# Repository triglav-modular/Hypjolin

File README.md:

# Hypjolin

The Hypjolin is a cross-modulating ultra-chaos generator device which combines Rob Hordijk’s Benjolin and Ian Fritz’s Hypster circuits. 
By merging the Benjolin’s stepped chaos with the Hypster’s smooth, fluctuating chaos, the Hypjolin produces remarkably unpredictable, yet controllable sonic outcomes.  
The integration of these two systems is facilitated through a banana jack patchbay, with blue banana jacks representing Benjolin outputs and purple ones denoting Hypster outputs. The black jacks serve as inputs. The patch bay is spaced for use with shorting bars.

Mouser Cart: https://www.mouser.com/ProjectManager/ProjectDetail.aspx?AccessID=39b2feea56

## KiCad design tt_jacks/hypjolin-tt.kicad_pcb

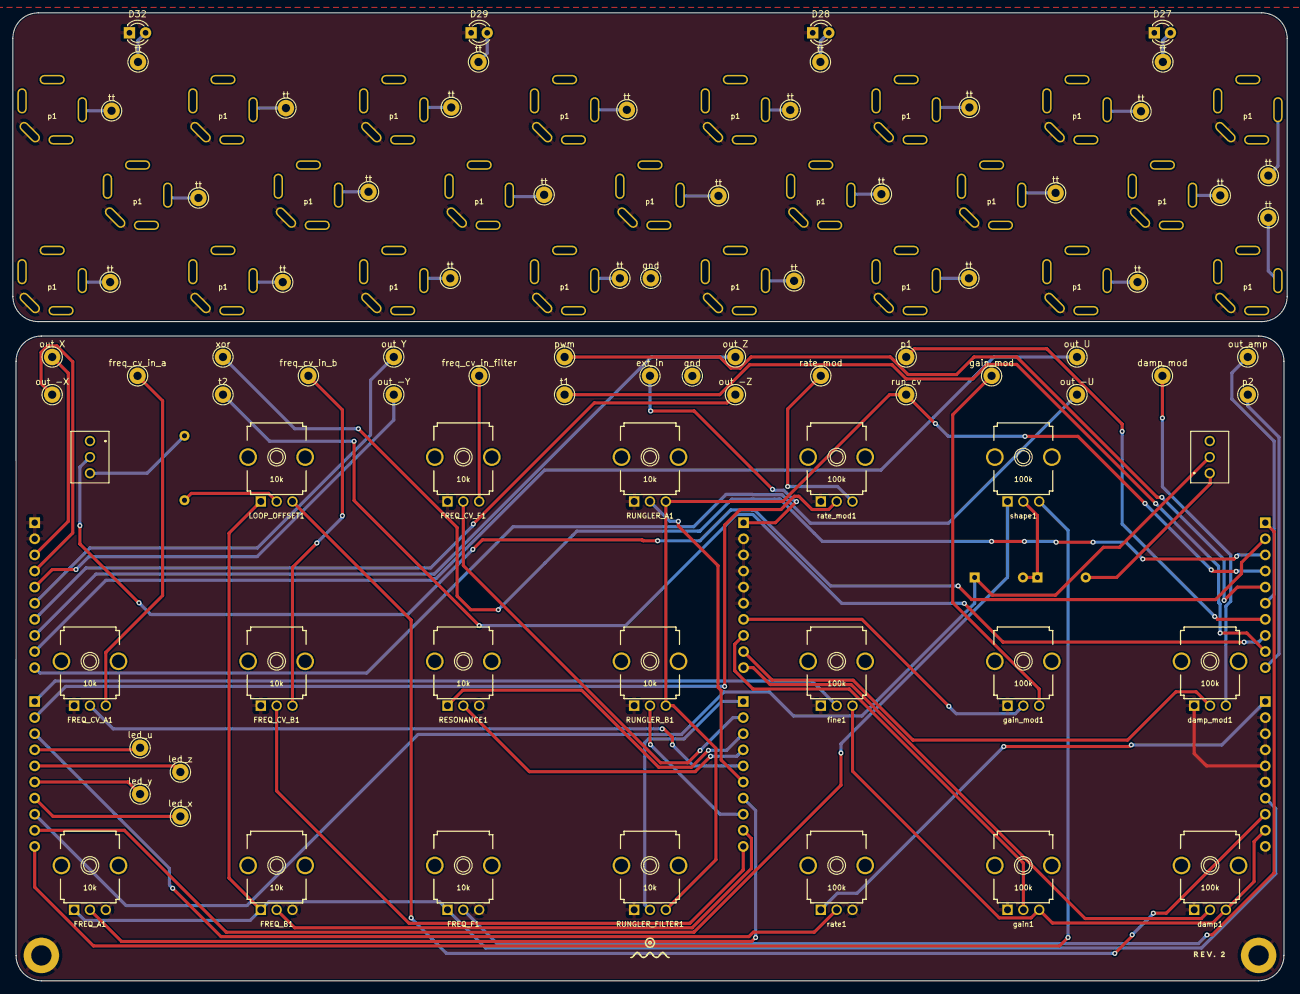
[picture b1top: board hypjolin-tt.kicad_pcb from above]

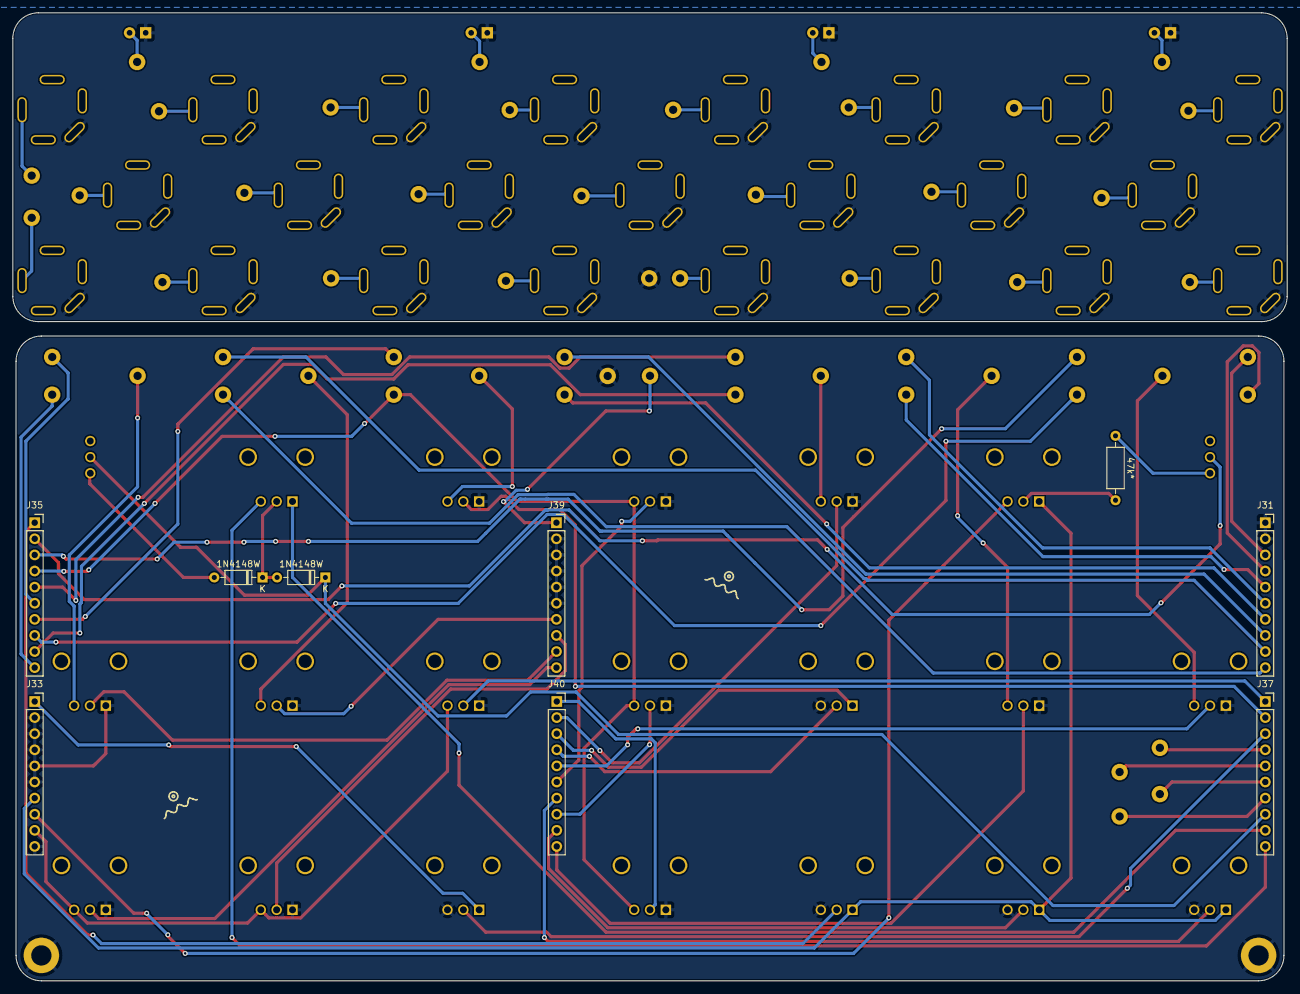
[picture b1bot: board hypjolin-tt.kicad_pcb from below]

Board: 2 copper layers, 201.0 x 152.7 mm, 113 parts (9 on the bottom side), 85 nets.

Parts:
D27: LED_Dual_Bidirectional_U; LED_D3.0mm_Clear
D28: LED_Dual_Bidirectional_Z; LED_D3.0mm_Clear
D29: LED_Dual_Bidirectional_Y; LED_D3.0mm_Clear
D30, D31: 1N4148W; D_DO-35_SOD27_P7.62mm_Horizontal
D32: LED_Dual_Bidirectional_X; LED_D3.0mm_Clear
FREQ_A1: 10k; MusicThingModular-9MM_SNAP-IN_POT
FREQ_B1: 10k; MusicThingModular-9MM_SNAP-IN_POT
FREQ_CV_A1: 10k; MusicThingModular-9MM_SNAP-IN_POT
FREQ_CV_B1: 10k; MusicThingModular-9MM_SNAP-IN_POT
FREQ_CV_F1: 10k; MusicThingModular-9MM_SNAP-IN_POT
FREQ_F1: 10k; MusicThingModular-9MM_SNAP-IN_POT
J1: freq_cv_in_a; Pin_D1.3mm_L11.0mm
J2: freq_cv_in_b; Pin_D1.3mm_L11.0mm
J3: ext_in; Pin_D1.3mm_L11.0mm
J4: p2; Pin_D1.3mm_L11.0mm
J5: t1; Pin_D1.3mm_L11.0mm
J6: t2; Pin_D1.3mm_L11.0mm
J7: p1; Pin_D1.3mm_L11.0mm
J8: out_amp; Pin_D1.3mm_L11.0mm
J9: pwm; Pin_D1.3mm_L11.0mm
J10: run_cv; Pin_D1.3mm_L11.0mm
J11: xor; Pin_D1.3mm_L11.0mm
J12: freq_cv_in_filter; Pin_D1.3mm_L11.0mm
J15: out -U; Pin_D1.3mm_L11.0mm
J16: out U; Pin_D1.3mm_L11.0mm
J17: out Z; Pin_D1.3mm_L11.0mm
J18: out -Z; Pin_D1.3mm_L11.0mm
J19: out Y; Pin_D1.3mm_L11.0mm
J20: out -Y; Pin_D1.3mm_L11.0mm
J21: out -X; Pin_D1.3mm_L11.0mm
J22: out X; Pin_D1.3mm_L11.0mm
J23: gain_mod; Pin_D1.3mm_L11.0mm
J24: rate_mod; Pin_D1.3mm_L11.0mm
J25: damp_mod; Pin_D1.3mm_L11.0mm
J31: CONN_4_P; PinSocket_1x10_P2.54mm_Vertical
J33: CONN_5_P; PinSocket_1x10_P2.54mm_Vertical
J35: CONN_2_P; PinSocket_1x10_P2.54mm_Vertical
J37: CONN_6_P; PinSocket_1x10_P2.54mm_Vertical
J39: CONN_1_P; PinSocket_1x10_P2.54mm_Vertical
J40: CONN_3_P; PinSocket_1x10_P2.54mm_Vertical
J43, J44, J45, J46, J47, J48, J49, J50, J51, J52, J53, J54, J55, J56, J57, J58, J59, J60, J61, J62, J63, J64, J65: p1; Bantam_TT
J66: led_u; Pin_D1.3mm_L11.0mm
J67: led_z; Pin_D1.3mm_L11.0mm
J68: led_y; Pin_D1.3mm_L11.0mm
J69: led_x; Pin_D1.3mm_L11.0mm
J70, J71: gnd; Pin_D1.3mm_L11.0mm
J72, J73, J74, J75, J76, J77, J78, J79, J80, J81, J82, J83, J84, J85, J86, J87, J88, J89, J90, J91, J92, J93, J94, J95, J96, J97, J98: tt; Pin_D1.3mm_L11.0mm
LOOP_OFFSET1: 10k; MusicThingModular-9MM_SNAP-IN_POT
R18: 47k*; R_Axial_DIN0207_L6.3mm_D2.5mm_P10.16mm_Horizontal
RESONANCE1: 10k; MusicThingModular-9MM_SNAP-IN_POT
RUNGLER_A1: 10k; MusicThingModular-9MM_SNAP-IN_POT
RUNGLER_B1: 10k; MusicThingModular-9MM_SNAP-IN_POT
RUNGLER_FILTER1: 10k; MusicThingModular-9MM_SNAP-IN_POT
SW1, SW2: SUBMINI_SPDT; 1082MS1T1B1M2QEEVX
damp1: 100k; MusicThingModular-9MM_SNAP-IN_POT
damp_mod1: 100k; MusicThingModular-9MM_SNAP-IN_POT
fine1: 100k; MusicThingModular-9MM_SNAP-IN_POT
gain1: 100k; MusicThingModular-9MM_SNAP-IN_POT
gain_mod1: 100k; MusicThingModular-9MM_SNAP-IN_POT
rate1: 100k; MusicThingModular-9MM_SNAP-IN_POT
rate_mod1: 100k; MusicThingModular-9MM_SNAP-IN_POT
shape1: 100k; MusicThingModular-9MM_SNAP-IN_POT

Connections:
/P / LEDU: J37.4, J66.1
/P / LEDX: J37.7, J69.1
/P / LEDY: J37.6, J68.1
/P / LEDZ: J37.5, J67.1
/P / OUT_AMP: J8.1, J35.6
/P / P1: J7.1, J35.7
/P / P2: J4.1, J35.10
/P / PWM: J9.1, J35.5
/P / RUN_CV: J10.1, J35.4, RUNGLER_A1.3 (E), RUNGLER_B1.3 (E), RUNGLER_FILTER1.3 (E)
/P / T1: J5.1, J35.9
/P / T2: J6.1, J35.8
/P / XOR: J11.1, J35.3
/P / cv_f_pot: FREQ_CV_F1.2 (S), J40.2
/P / damp_mod: J25.1, damp_mod1.3 (E)
/P / damp_mod_pot: J39.9, damp_mod1.2 (S)
/P / damp_pot: J39.10, damp1.2 (S)
/P / ext_in: J3.1, J39.1
/P / fine_pot: J37.1, fine1.2 (S)
/P / freq_a_pot: FREQ_A1.2 (S), J40.7
/P / freq_b_pot: FREQ_B1.2 (S), J40.9
/P / freq_cv_a_pot: FREQ_CV_A1.2 (S), J40.5
/P / freq_cv_b_pot: FREQ_CV_B1.2 (S), J40.10
/P / freq_f_pot: FREQ_F1.2 (S), J35.1
/P / gain_mod: J23.1, gain_mod1.3 (E)
/P / gain_mod_pot: J39.7, gain_mod1.2 (S)
/P / gain_pot: J39.8, gain1.2 (S)
/P / offset_switch: J35.2, SW1.2 (COMMON)
/P / out -U: J15.1, J31.10
/P / out -X: J21.1, J31.4
/P / out -Y: J20.1, J31.5
/P / out -Z: J18.1, J31.7
/P / out U: J16.1, J31.9
/P / out X: J22.1, J31.3
/P / out Y: J19.1, J31.6
/P / out Z: J17.1, J31.8
/P / rate_mod: J24.1, rate_mod1.3 (E)
/P / rate_mod_pot: J37.2, rate_mod1.2 (S)
/P / rate_pot: J37.3, rate1.2 (S)
/P / reso_pot_A: J40.4, RESONANCE1.2 (S)
/P / reso_pot_B: J40.3, RESONANCE1.1 (A)
/P / run_a_pot: J40.6, RUNGLER_A1.2 (S)
/P / run_b_pot: J40.8, RUNGLER_B1.2 (S)
/P / run_f_pot: J40.1, RUNGLER_FILTER1.2 (S)
/P / shape_IN1: J37.10, shape1.3 (E)
/P / shape_IN2: J37.9, shape1.1 (A)
/P / shape_OUT: D30.1 (K), J37.8, SW2.2 (COMMON)
unnamed: D27.2 (AK), J95.1
unnamed: D28.2 (AK), J96.1
unnamed: D29.2 (AK), J97.1
unnamed: D30.2 (A), D31.1 (K), shape1.2 (S)
unnamed: D31.2 (A), SW2.1 (O)
unnamed: D32.2 (AK), J98.1
unnamed: FREQ_CV_A1.3 (E), J1.1
unnamed: FREQ_CV_B1.3 (E), J2.1
unnamed: FREQ_CV_F1.3 (E), J12.1
unnamed: J43.3 (T), J72.1
unnamed: J44.3 (T), J74.1
unnamed: J45.3 (T), J73.1
unnamed: J46.3 (T), J75.1
unnamed: J47.3 (T), J76.1
unnamed: J48.3 (T), J77.1
unnamed: J49.3 (T), J78.1
unnamed: J50.3 (T), J79.1
unnamed: J51.3 (T), J80.1
unnamed: J52.3 (T), J81.1
unnamed: J53.3 (T), J82.1
unnamed: J54.3 (T), J83.1
unnamed: J55.3 (T), J84.1
unnamed: J56.3 (T), J85.1
unnamed: J57.3 (T), J86.1
unnamed: J58.3 (T), J87.1
unnamed: J59.3 (T), J88.1
unnamed: J60.3 (T), J89.1
unnamed: J61.3 (T), J90.1
unnamed: J62.3 (T), J91.1
unnamed: J63.3 (T), J92.1
unnamed: J64.3 (T), J93.1
unnamed: J65.3 (T), J94.1
unnamed: LOOP_OFFSET1.2 (S), R18.1
unnamed: R18.2, SW1.3 (S)
P / GND: D27.1 (KA), D28.1 (KA), D29.1 (KA), D32.1 (KA), FREQ_A1.3 (E), FREQ_B1.3 (E), FREQ_CV_A1.1 (A), FREQ_CV_B1.1 (A), FREQ_CV_F1.1 (A), FREQ_F1.3 (E), J31.1, J31.2, J33.2, J33.3, J33.4, J33.5, J33.6, J33.10, J39.2, J39.3, J39.4, J39.5, J39.6, J43.1 (S), J44.1 (S), J45.1 (S), J46.1 (S), J47.1 (S), J48.1 (S), J49.1 (S), J50.1 (S), J51.1 (S), J52.1 (S), J53.1 (S), J54.1 (S), J55.1 (S), J56.1 (S), J57.1 (S), J58.1 (S), J59.1 (S), J60.1 (S), J61.1 (S), J62.1 (S), J63.1 (S), J64.1 (S), J65.1 (S), J70.1, J71.1, RESONANCE1.3 (E), RUNGLER_A1.1 (A), RUNGLER_B1.1 (A), RUNGLER_FILTER1.1 (A), damp1.1 (A), damp_mod1.1 (A), fine1.1 (A), gain1.1 (A), gain_mod1.1 (A), rate1.3 (E), rate_mod1.1 (A)
P / V+: J33.8, LOOP_OFFSET1.3 (E)
P / V-: FREQ_A1.1 (A), FREQ_B1.1 (A), FREQ_F1.1 (A), J33.7, LOOP_OFFSET1.1 (A)
P / VCC: J33.9, damp1.3 (E), fine1.3 (E), gain1.3 (E)
P / VEE: J33.1, rate1.1 (A)

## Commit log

2022-08-25 routed signals
2022-08-25 routed all tracks
2022-08-25 prettified some tracks
2022-08-25 prettyfied tracks
2022-08-25 cleanup tracks
2022-08-25 board cleanup
2022-08-26 cleanup / fixes
2022-08-26 graphics
2022-08-29 add mounting holes, wider power tracks
2022-08-29 silkscreen fixes
2022-08-29 fixes, cleanup
2022-08-29 cleanup
2022-08-31 silkscreen, trace cleanup
2022-08-31 track cleanup
2022-08-31 alpha_1
2022-08-31 cleanup folders
2022-08-31 track cleanup, 3D model update
2022-08-31 fab file update
2022-09-05 board fixes
2022-09-19 first prototype
2022-11-16 Rev.2
    Fix issues with rev.1, add TT version
2023-01-05 Bantam panel
2023-04-21 Create LICENSE
2023-07-19 Cleaned up panel graphics file
2023-07-19 Outlined text
2023-07-21 Added box and manual
